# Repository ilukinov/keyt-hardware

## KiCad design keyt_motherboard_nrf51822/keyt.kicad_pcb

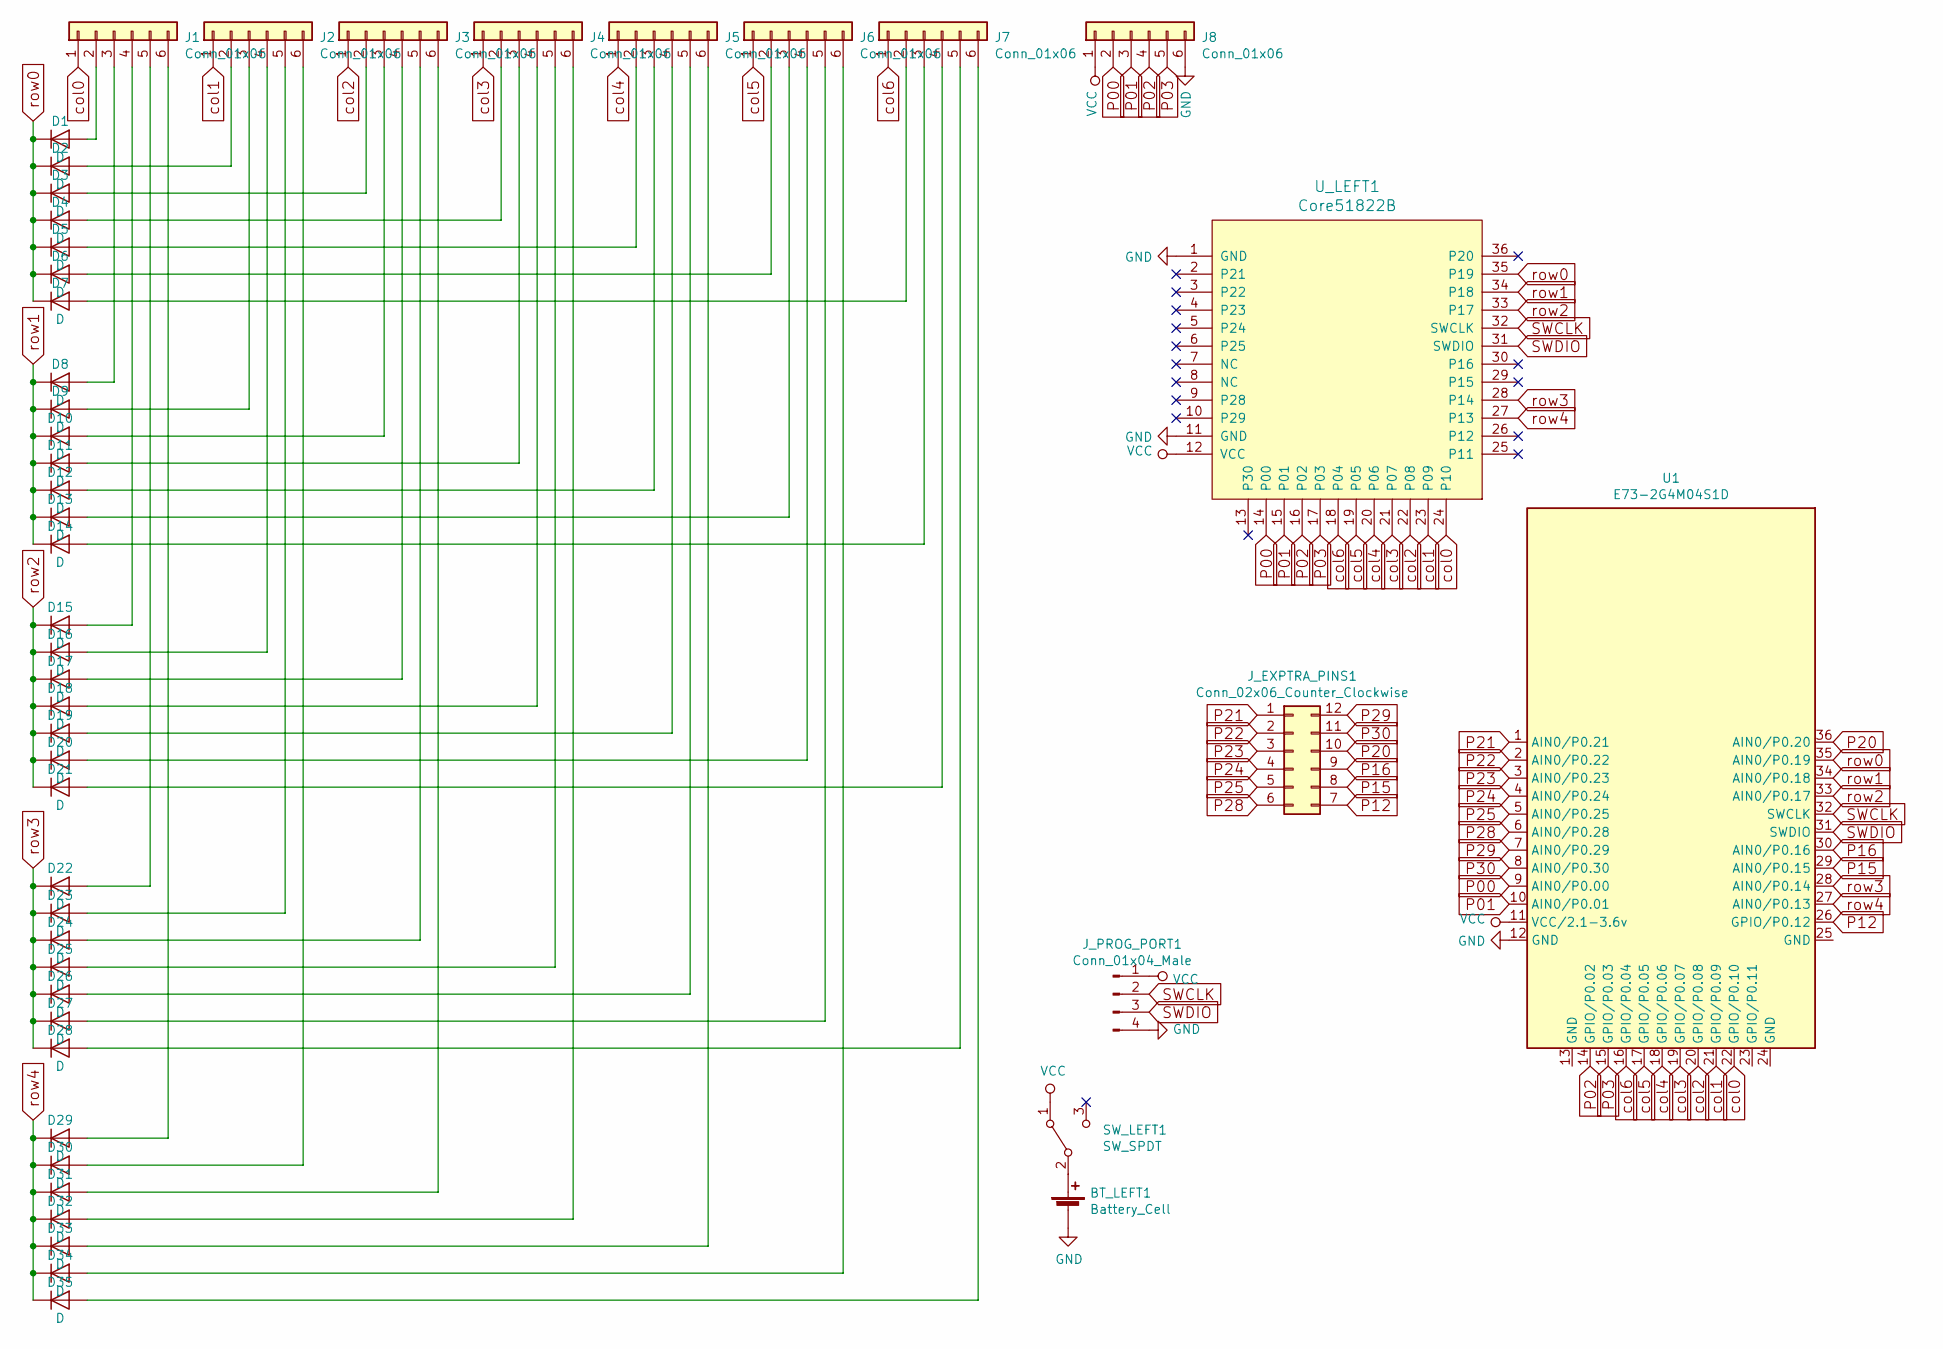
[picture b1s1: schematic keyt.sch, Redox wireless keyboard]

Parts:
BT_LEFT1: Battery_Cell; BatteryHolder_Keystone_3034_1x20mm
D1, D2, D3, D4, D5, D6, D7, D8, D9, D10, D11, D12, D13, D14, D15, D16, D17, D18, D19, D20, D21, D22, D23, D24, D25, D26, D27, D28, D29, D30, D31, D32, D33, D34, D35: D; D_SOD-123F_HIDE
J1, J2, J3, J4, J5, J6, J7, J8: Conn_01x06; JST_SHL_SM06B-SHLS-TF_1x06-1MP_P1.00mm_Horizontal
J_EXPTRA_PINS1: Conn_02x06_Counter_Clockwise; PinSocket_2x06_P2.54mm_Vertical
J_PROG_PORT1: Conn_01x04_Male; PinHeader_1x04_P2.54mm_Vertical
SW_LEFT1: SW_SPDT; SK12D07VG3
U1: E73-2G4M04S1D
U_LEFT1: Core51822B; MY-YJ-14015-Module

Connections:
GND: BT_LEFT1.2 (-), J8.6, J_PROG_PORT1.4, U1.12 (GND), U_LEFT1.1 (GND), U_LEFT1.11 (GND)
unnamed: BT_LEFT1.1 (+), SW_LEFT1.2 (B)
unnamed: D1.2 (A), J1.2
unnamed: D2.2 (A), J2.2
unnamed: D3.2 (A), J3.2
unnamed: D4.2 (A), J4.2
unnamed: D5.2 (A), J5.2
unnamed: D6.2 (A), J6.2
unnamed: D7.2 (A), J7.2
unnamed: D8.2 (A), J1.3
unnamed: D9.2 (A), J2.3
unnamed: D10.2 (A), J3.3
unnamed: D11.2 (A), J4.3
unnamed: D12.2 (A), J5.3
unnamed: D13.2 (A), J6.3
unnamed: D14.2 (A), J7.3
unnamed: D15.2 (A), J1.4
unnamed: D16.2 (A), J2.4
unnamed: D17.2 (A), J3.4
unnamed: D18.2 (A), J4.4
unnamed: D19.2 (A), J5.4
unnamed: D20.2 (A), J6.4
unnamed: D21.2 (A), J7.4
unnamed: D22.2 (A), J1.5
unnamed: D23.2 (A), J2.5
unnamed: D24.2 (A), J3.5
unnamed: D25.2 (A), J4.5
unnamed: D26.2 (A), J5.5
unnamed: D27.2 (A), J6.5
unnamed: D28.2 (A), J7.5
unnamed: D29.2 (A), J1.6
unnamed: D30.2 (A), J2.6
unnamed: D31.2 (A), J3.6
unnamed: D32.2 (A), J4.6
unnamed: D33.2 (A), J5.6
unnamed: D34.2 (A), J6.6
unnamed: D35.2 (A), J7.6
P00: J8.2, U1.9 (AIN0/P0.00), U_LEFT1.14 (P00)
P01: J8.3, U1.10 (AIN0/P0.01), U_LEFT1.15 (P01)
P02: J8.4, U1.14 (GPIO/P0.02), U_LEFT1.16 (P02)
P03: J8.5, U1.15 (GPIO/P0.03), U_LEFT1.17 (P03)
P12: J_EXPTRA_PINS1.7, U1.26 (GPIO/P0.12)
P15: J_EXPTRA_PINS1.8, U1.29 (AIN0/P0.15)
P16: J_EXPTRA_PINS1.9, U1.30 (AIN0/P0.16)
P20: J_EXPTRA_PINS1.10, U1.36 (AIN0/P0.20)
P21: J_EXPTRA_PINS1.1, U1.1 (AIN0/P0.21)
P22: J_EXPTRA_PINS1.2, U1.2 (AIN0/P0.22)
P23: J_EXPTRA_PINS1.3, U1.3 (AIN0/P0.23)
P24: J_EXPTRA_PINS1.4, U1.4 (AIN0/P0.24)
P25: J_EXPTRA_PINS1.5, U1.5 (AIN0/P0.25)
P28: J_EXPTRA_PINS1.6, U1.6 (AIN0/P0.28)
P29: J_EXPTRA_PINS1.12, U1.7 (AIN0/P0.29)
P30: J_EXPTRA_PINS1.11, U1.8 (AIN0/P0.30)
SWCLK: J_PROG_PORT1.2, U1.32 (SWCLK), U_LEFT1.32 (SWCLK)
SWDIO: J_PROG_PORT1.3, U1.31 (SWDIO), U_LEFT1.31 (SWDIO)
VCC: J8.1, J_PROG_PORT1.1, SW_LEFT1.1 (A), U1.11 (VCC/2.1-3.6v), U_LEFT1.12 (VCC)
col0: J1.1, U1.22 (GPIO/P0.10), U_LEFT1.24 (P10)
col1: J2.1, U1.21 (GPIO/P0.09), U_LEFT1.23 (P09)
col2: J3.1, U1.20 (GPIO/P0.08), U_LEFT1.22 (P08)
col3: J4.1, U1.19 (GPIO/P0.07), U_LEFT1.21 (P07)
col4: J5.1, U1.18 (GPIO/P0.06), U_LEFT1.20 (P06)
col5: J6.1, U1.17 (GPIO/P0.05), U_LEFT1.19 (P05)
col6: J7.1, U1.16 (GPIO/P0.04), U_LEFT1.18 (P04)
row0: D1.1 (K), D2.1 (K), D3.1 (K), D4.1 (K), D5.1 (K), D6.1 (K), D7.1 (K), U1.35 (AIN0/P0.19), U_LEFT1.35 (P19)
row1: D8.1 (K), D9.1 (K), D10.1 (K), D11.1 (K), D12.1 (K), D13.1 (K), D14.1 (K), U1.34 (AIN0/P0.18), U_LEFT1.34 (P18)
row2: D15.1 (K), D16.1 (K), D17.1 (K), D18.1 (K), D19.1 (K), D20.1 (K), D21.1 (K), U1.33 (AIN0/P0.17), U_LEFT1.33 (P17)
row3: D22.1 (K), D23.1 (K), D24.1 (K), D25.1 (K), D26.1 (K), D27.1 (K), D28.1 (K), U1.28 (AIN0/P0.14), U_LEFT1.28 (P14)
row4: D29.1 (K), D30.1 (K), D31.1 (K), D32.1 (K), D33.1 (K), D34.1 (K), D35.1 (K), U1.27 (AIN0/P0.13), U_LEFT1.27 (P13)

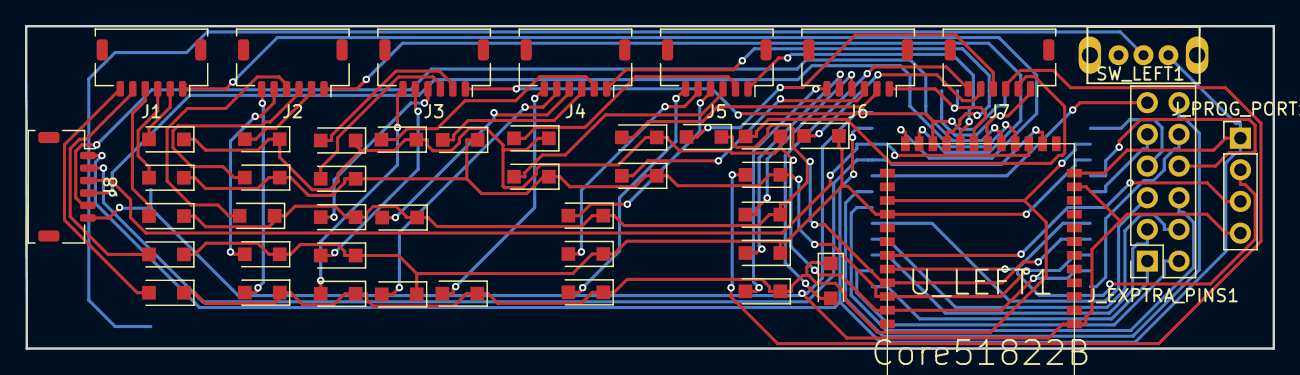
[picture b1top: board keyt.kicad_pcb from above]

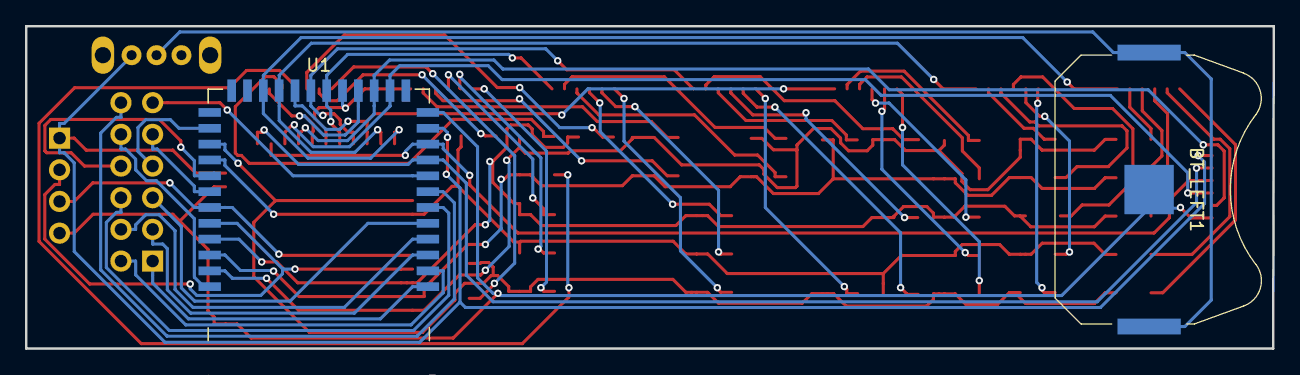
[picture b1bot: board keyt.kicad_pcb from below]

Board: 2 copper layers, 100.1 x 25.8 mm, 49 parts (2 on the bottom side), 68 nets.

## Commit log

2021-02-17 Cleaning up
